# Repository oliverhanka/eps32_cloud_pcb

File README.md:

# ESP32 low power sensor node

This is a simplistic ESP32 based sensor node with a focus on very low power consumption while beeing idle. This means, external components are keept to a minimum and the selected LDO has a very low power consumption. The board can be supplied with 3.3V directly or by using the on-board LDO (max. 6V input) to generate the required 3.3V. *NOTE: The LDO_EN solder jumper must be closed in order to use the LDO.*

#### Theoretical power consumption
These values have not been verified by measurements and do not take the passive components into account.

Power consumption while beeing in hibernation:
| Active component | Current | Power |
| -------- | -------- | -------- |
| ESP32 (in hibernation)  | 5𝜇A @ 3.3V  | 16.5𝜇W |
| LDO  | 8𝜇A @ 5V  | 40𝜇W |
| **Total**  | **11.3𝜇A @ 5V**  | **56.5𝜇W** |

While beeing active and transmitting via Wifi (BLE off):
| Active component | Current | Power |
| -------- | -------- | -------- |
| ESP32 (240MHz, Wifi tx)  | 240mA @ 3.3V  | 792mW |
| LDO  | 8𝜇A @ 5V  | 40𝜇W |
| **Total**  | **158.4mA @ 5V**  | **792mW** |

## Connectors / headers / solder jumper

| Connector | Purpose |
| -------- | -------- |
| J1     | I2C, power via GPIO14     |
| J2     | power connector, JST-PH     |
| J3     | power connector, USB-C     |
| J4     | programming interface, compatible with [ESP-Prog](https://github.com/espressif/esp-iot-solution/blob/master/documents/evaluation_boards/ESP-Prog_guide_en.md)     |
| J5     | various GPIOs or ADC and SPI, VCC, GND     |
| J6     | GPIO (e.g., for WS2812, power via GPIO2)     |

| Solder jumper | Purpose |
| -------- | -------- |
| LED_EN     | Enable blue LED D1 controlled by GPIO12)     |
| LDO_EN     | Enable LDO (e.g., for power via USB-C)     |

## Build

### Manufactured PCB 
 | 
------------ | -------------
frontside rev 1.0 | backside rev 1.0

### Assembled PCB

 | 
------------ | -------------
assembled front rev 1.0 | assembled back rev 1.0

### Bill of materials (BOM)

| Designator | Manufacturer Part Number | Qty |
| -------- | -------- |	-------- |	
|J6, J2 |	S3B-PH-SM4-TB(LF)(SN) |	2 |
|J1 |	S4B-PH-SM4-TB(LF)(SN) |	1 |
|J3 |	TYPE-C-31-M-12 |	1 |
|R1 |	10kΩ (0603) |	1 |
|R2 |	330Ω (0603) |	1 |
|D1 |	LED (0603) |	1 |
|L1 |	1.6nH (0603) |	1 |
|C7 |	22uF (0603) |	1 |
|C6 |	0.1uf (0603) |	1 |
|C5, C3 |	0.1uF/25V (0603) |	2 |
|C4 |	10uF/6.3V (0603) |	1 |
|C2 |	2.7pF (0603) |	1 |
|C1 |	4.7pF (0603) |	1 |
|U1 |	ESP32-PICO-D4 |	1 |
|U3 |	XC6220B331MR-G |	1 |

---

## Changelog
rev 1.2
- **BREAKING CHANGE**: J6 GPIOs reassigned to GPIO 32 and GPIO 33. GPIO 32 & 33 can be used as ADC1 channels.

rev 1.1
- FIX: U3's EN pin pulled to VCC

rev 1.0
- Initial PCB layout

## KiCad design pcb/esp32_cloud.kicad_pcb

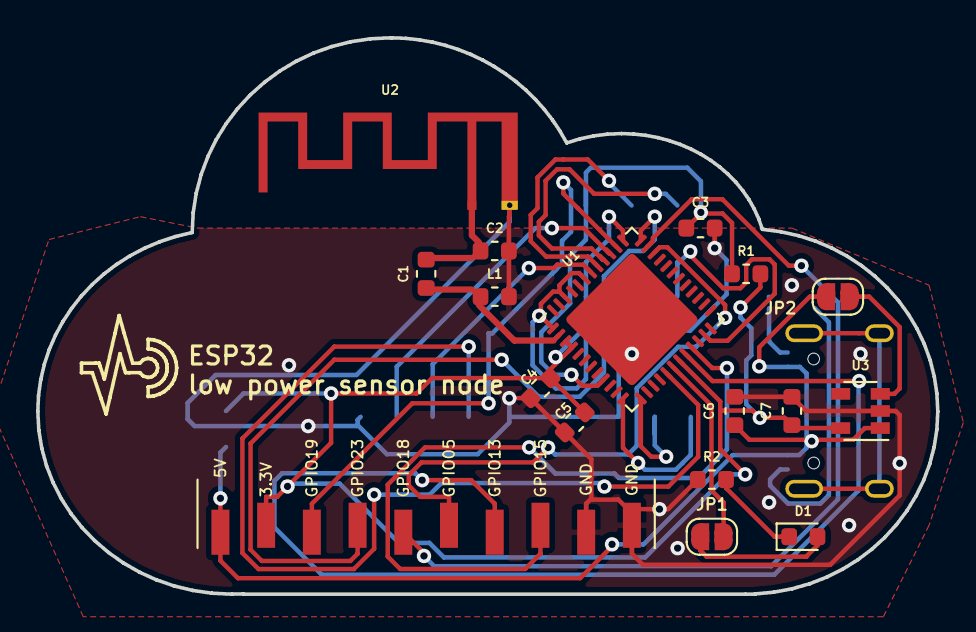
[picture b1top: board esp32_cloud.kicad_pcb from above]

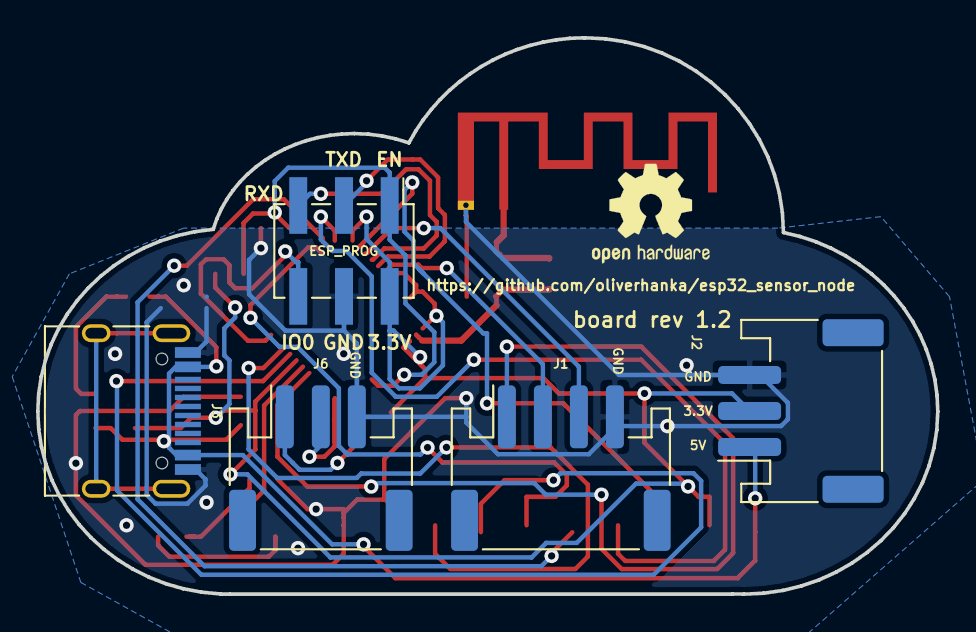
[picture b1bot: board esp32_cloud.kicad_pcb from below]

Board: 2 copper layers, 50.0 x 30.9 mm, 22 parts (5 on the bottom side), 24 nets.

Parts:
C1: 4.7pF; C_0603_1608Metric
C2: 2.7pF; C_0603_1608Metric
C3, C5: 0.1uF/25V; C_0603_1608Metric
C4: 10uF/6.3V; C_0603_1608Metric
C6: 0.1uF; C_0603_1608Metric
C7: 22uF; C_0603_1608Metric
D1: LED; LED_0603_1608Metric
J1: Conn_01x04_Male; JST_PH_S4B-PH-SM4-TB_1x04-1MP_P2.00mm_Horizontal
J2, J6: Conn_01x03_Male; JST_PH_S3B-PH-SM4-TB_1x03-1MP_P2.00mm_Horizontal
J3: USB_C_Receptacle_USB2.0; USB_C_Receptacle_HRO_TYPE-C-31-M-12
J4: Conn_01x06_Male; PinHeader_2x03_P2.54mm_Vertical_SMD
J5: Conn_01x10_Male; PinHeader_1x10_P2.54mm_Vertical_SMD_Pin1Left
JP1, JP2: Jumper_NO_Small; SolderJumper-2_P1.3mm_Open_RoundedPad1.0x1.5mm
L1: 1.6nH; L_0603_1608Metric
R1: 10k; R_0603_1608Metric
R2: 330; R_0603_1608Metric
U1: ESP32-PICO-D4; QFN-48-1EP_7x7mm_P0.5mm_EP5.3x5.3mm
U2: AN91445; Texas_SWRA117D_2.4GHz_Left
U3: XC6220B331MR; SOT-23-5

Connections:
+3.3VA: C4.1, C5.1, C7.1, J2.2, J4.2, J5.2, R1.1, U1.1, U1.3, U1.4, U1.19, U1.37, U1.43, U1.46, U3.5
+5V: C6.1, J2.1, J3.A4, J3.A9, J3.B4, J3.B9, J5.1, JP2.2, U3.1
/BME280_SCL: J1.3, U1.39
/BME280_SDA: J1.2, U1.42
/BME280_VCC: J1.1, U1.17
/EN: C3.1, J4.1, R1.2, U1.9
/GPIO5_CS0: J5.6, U1.34
/GPIO13_ADC2_CH4: J5.7, U1.20
/GPIO15_ADC2_CH3: J5.8, U1.21
/GPIO18_CLK: J5.5, U1.35
/GPIO19_MISO: J5.3, U1.38
/GPIO23_MOSI: J5.4, U1.36
/GPIO32: J6.1, U1.12
/GPIO33: J6.2, U1.13
/IO0: J4.6, U1.23
/LED_GPIO: JP1.2, U1.18
/RXD: J4.5, U1.40
/TXD: J4.3, U1.41
GND: C2.1, C3.2, C4.2, C5.2, C6.2, C7.2, J1.4, J2.3, J3.A1, J3.A12, J3.B1, J3.B12, J4.4, J5.9, J5.10, J6.3, L1.1, R2.2, U1.49, U2.2, U3.2
unnamed: C1.1, C2.2, U2.1
unnamed: C1.2, L1.2, U1.2
unnamed: D1.1, R2.1
unnamed: D1.2, JP1.1
unnamed: JP2.1, U3.3

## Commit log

2020-04-09 rev 1.1
2020-04-21 J6 changed from ADC2 to ADC1 GPIOs
